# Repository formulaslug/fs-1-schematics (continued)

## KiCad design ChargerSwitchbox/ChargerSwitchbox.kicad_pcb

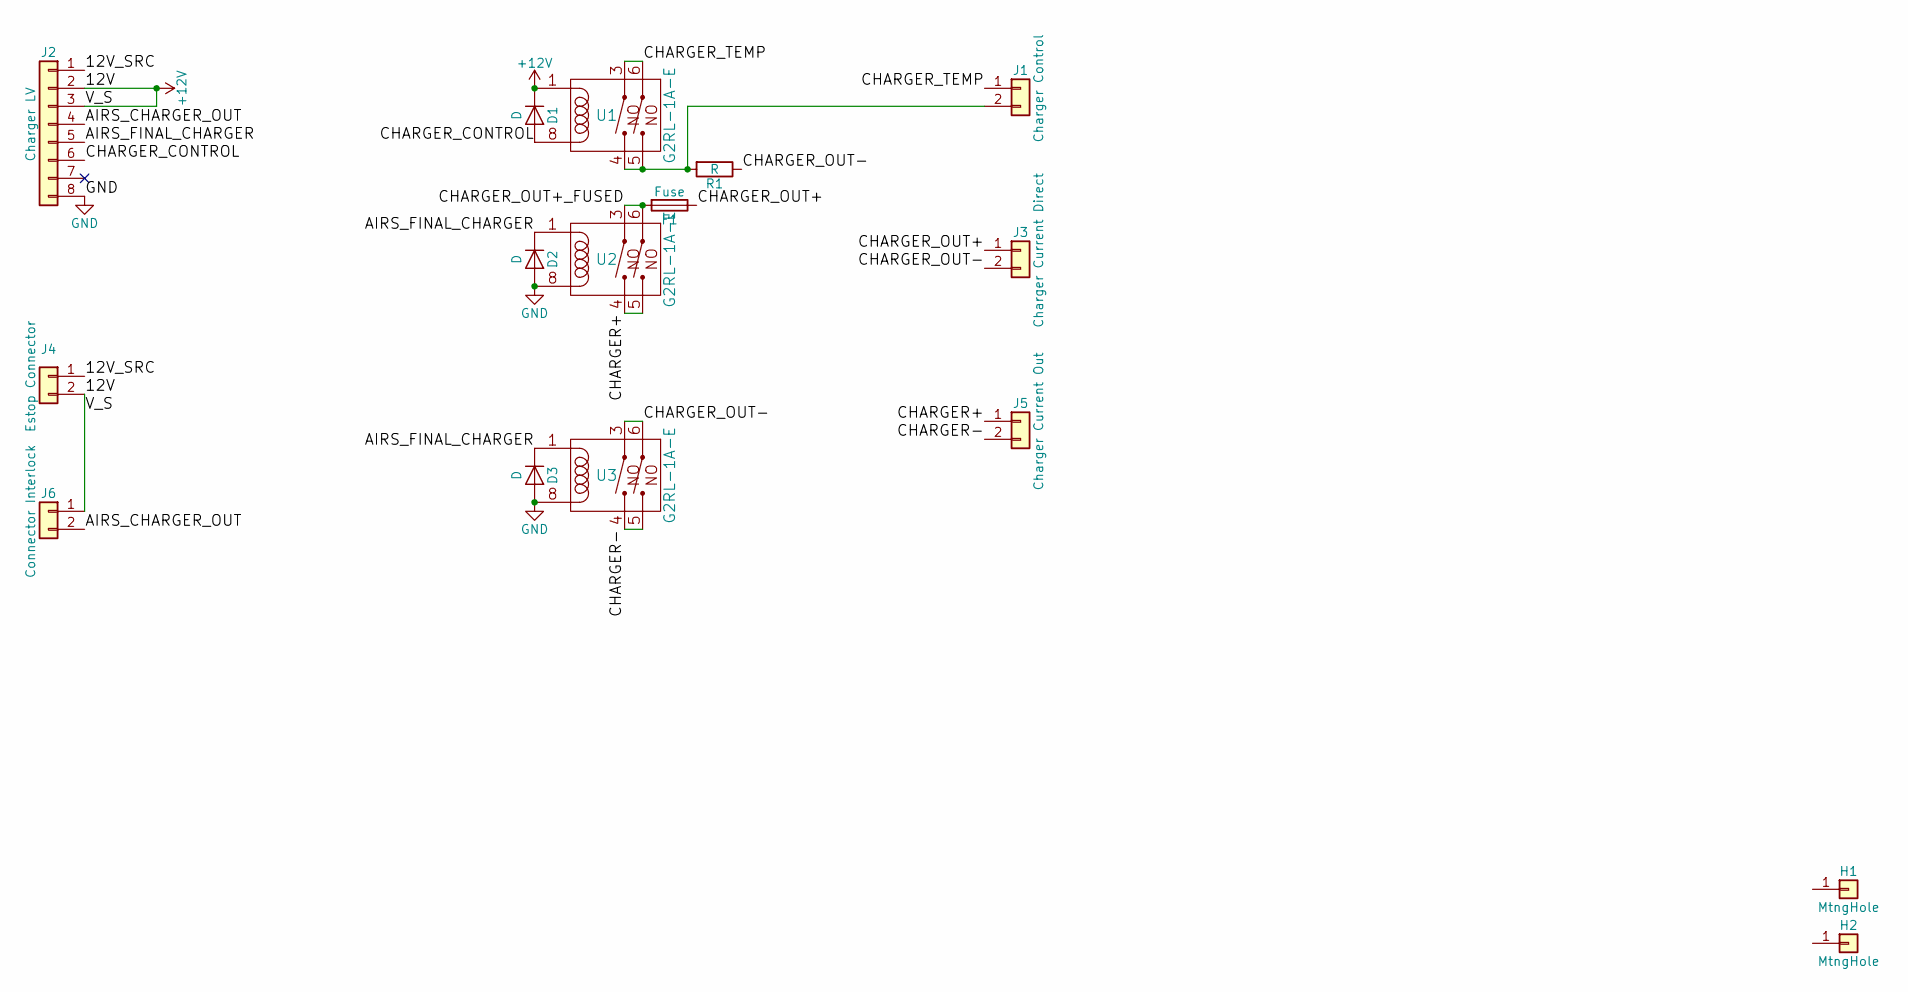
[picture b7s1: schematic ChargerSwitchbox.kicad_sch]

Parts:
D1, D2, D3: D; D_1206
F1: Fuse; Fuseholder5x20_vert
H1, H2: MtngHole; MountingHole_4.5mm
J1: Charger Control; Molex_NanoFit_1x02x2.50mm_Straight
J2: Charger LV; Ampseal - 8 pin
J3: Charger Current Direct; Molex_MiniFit-JR-5556-02A_2x01x4.20mm_Straight
J4: Estop Connector; Molex_NanoFit_1x02x2.50mm_Straight
J5: Charger Current Out; Molex_MiniFit-JR-5556-02A_2x01x4.20mm_Straight
J6: Connector Interlock; Molex_NanoFit_1x02x2.50mm_Straight
R1: R; SMDNetTie
U1, U2, U3: G2RL-1A-E

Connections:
+12V: D1.1 (K), J2.2, J2.3, J4.2, J6.1, U1.1
/12V_SRC: J2.1, J4.1
/AIRS_CHARGER_OUT: J2.4, J6.2
/AIRS_FINAL_CHARGER: D2.1 (K), D3.1 (K), J2.5, U2.1, U3.1
/CHARGER+: J5.1, U2.4, U2.5
/CHARGER-: J5.2, U3.4, U3.5
/CHARGER_CONTROL: D1.2 (A), J2.6, U1.8
/CHARGER_OUT+: F1.1, J3.1
/CHARGER_OUT+_FUSED: F1.2, U2.3, U2.6
/CHARGER_OUT-: J3.2, R1.1, U3.3, U3.6
/CHARGER_TEMP: J1.1, U1.3, U1.6
GND: D2.2 (A), D3.2 (A), J2.8, U2.8, U3.8
unnamed: J1.2, R1.2, U1.4, U1.5

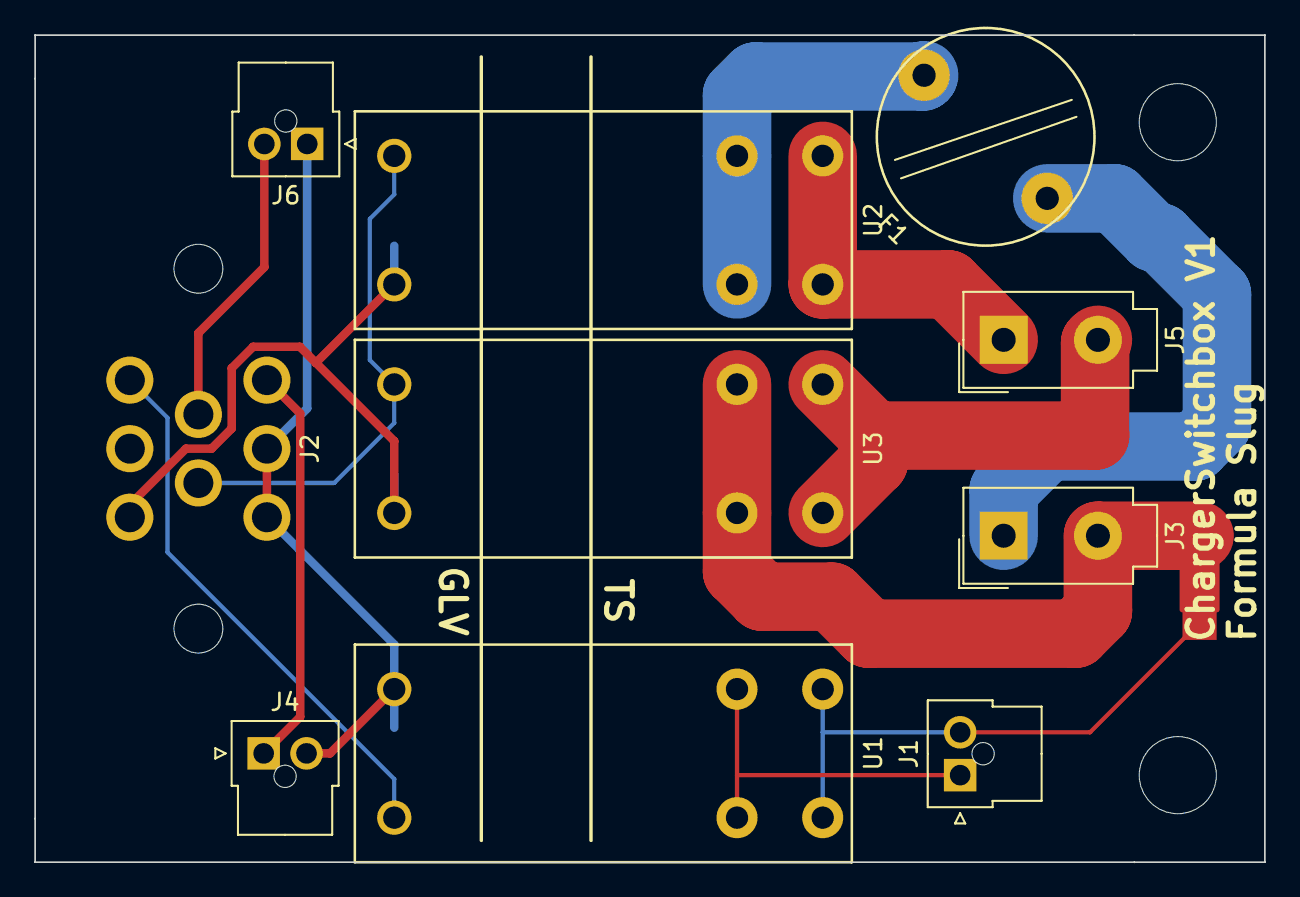
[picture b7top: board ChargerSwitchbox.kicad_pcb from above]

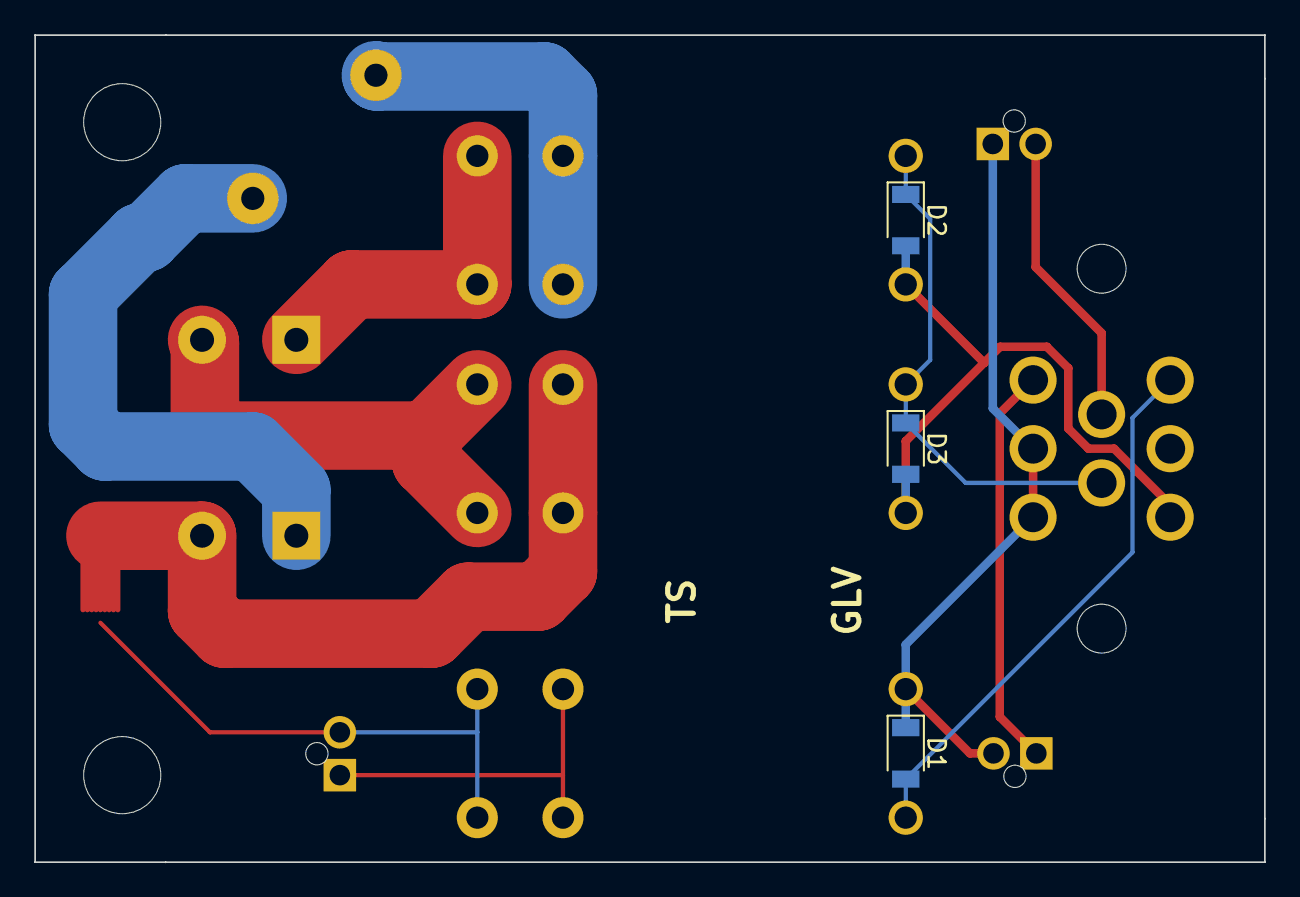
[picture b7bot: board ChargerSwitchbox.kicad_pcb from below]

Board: 2 copper layers, 71.8 x 48.3 mm, 16 parts (3 on the bottom side), 13 nets.

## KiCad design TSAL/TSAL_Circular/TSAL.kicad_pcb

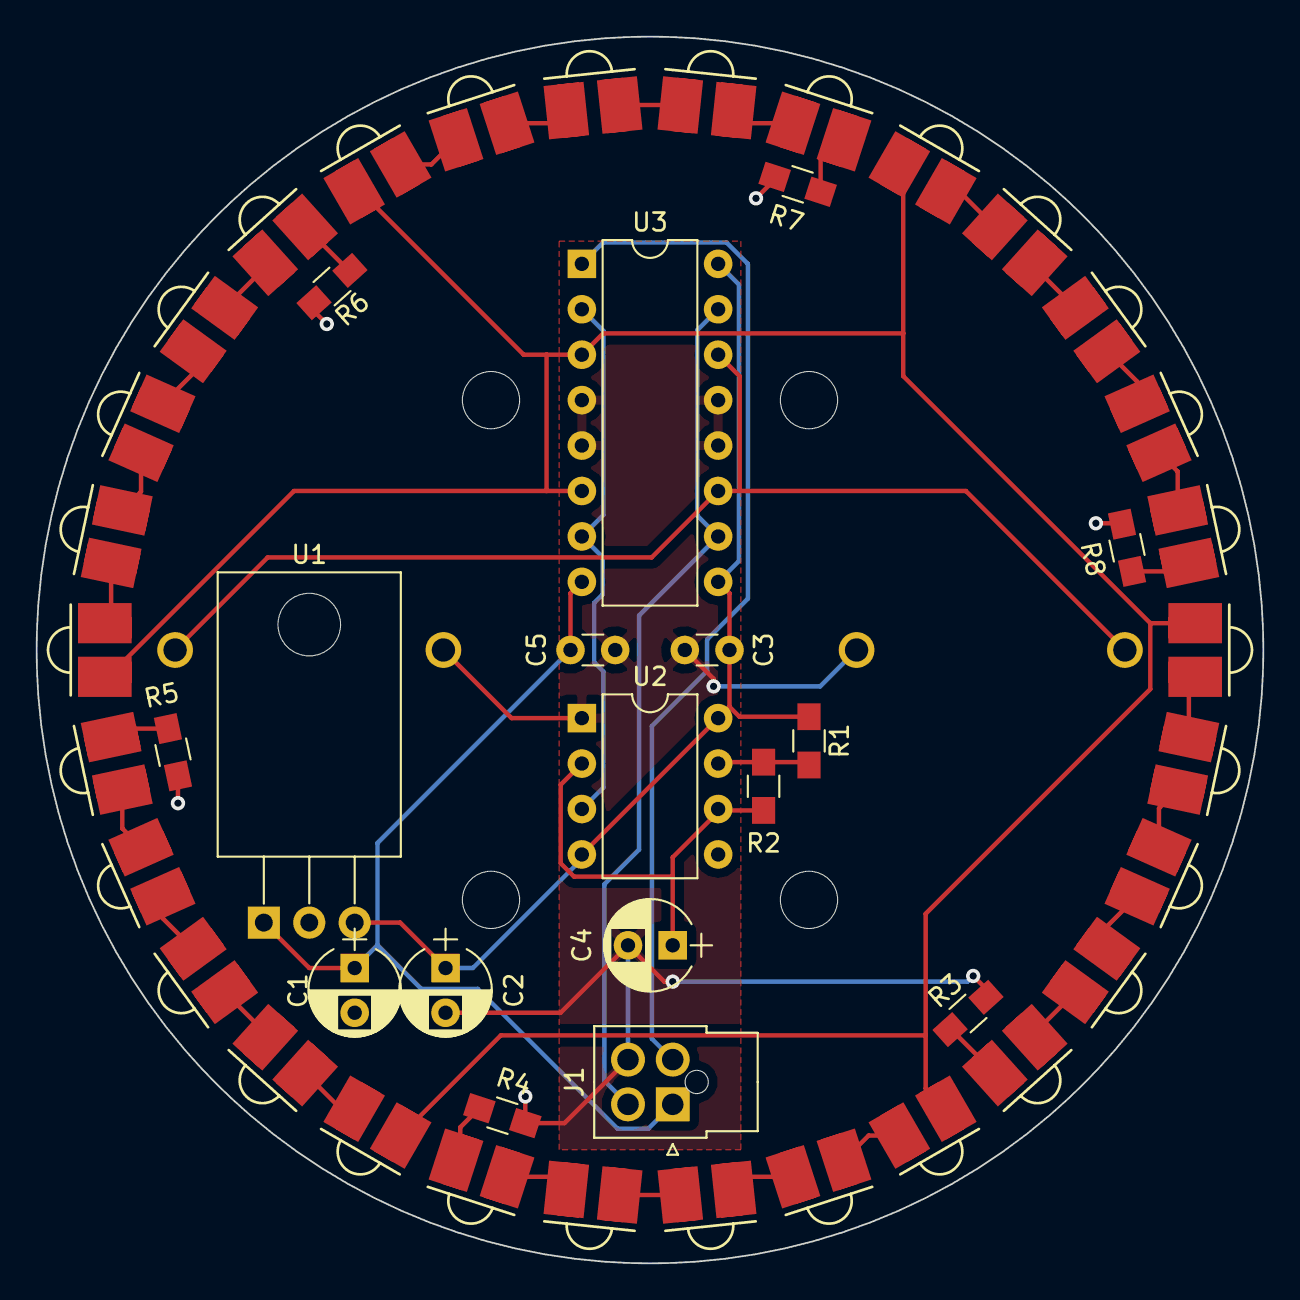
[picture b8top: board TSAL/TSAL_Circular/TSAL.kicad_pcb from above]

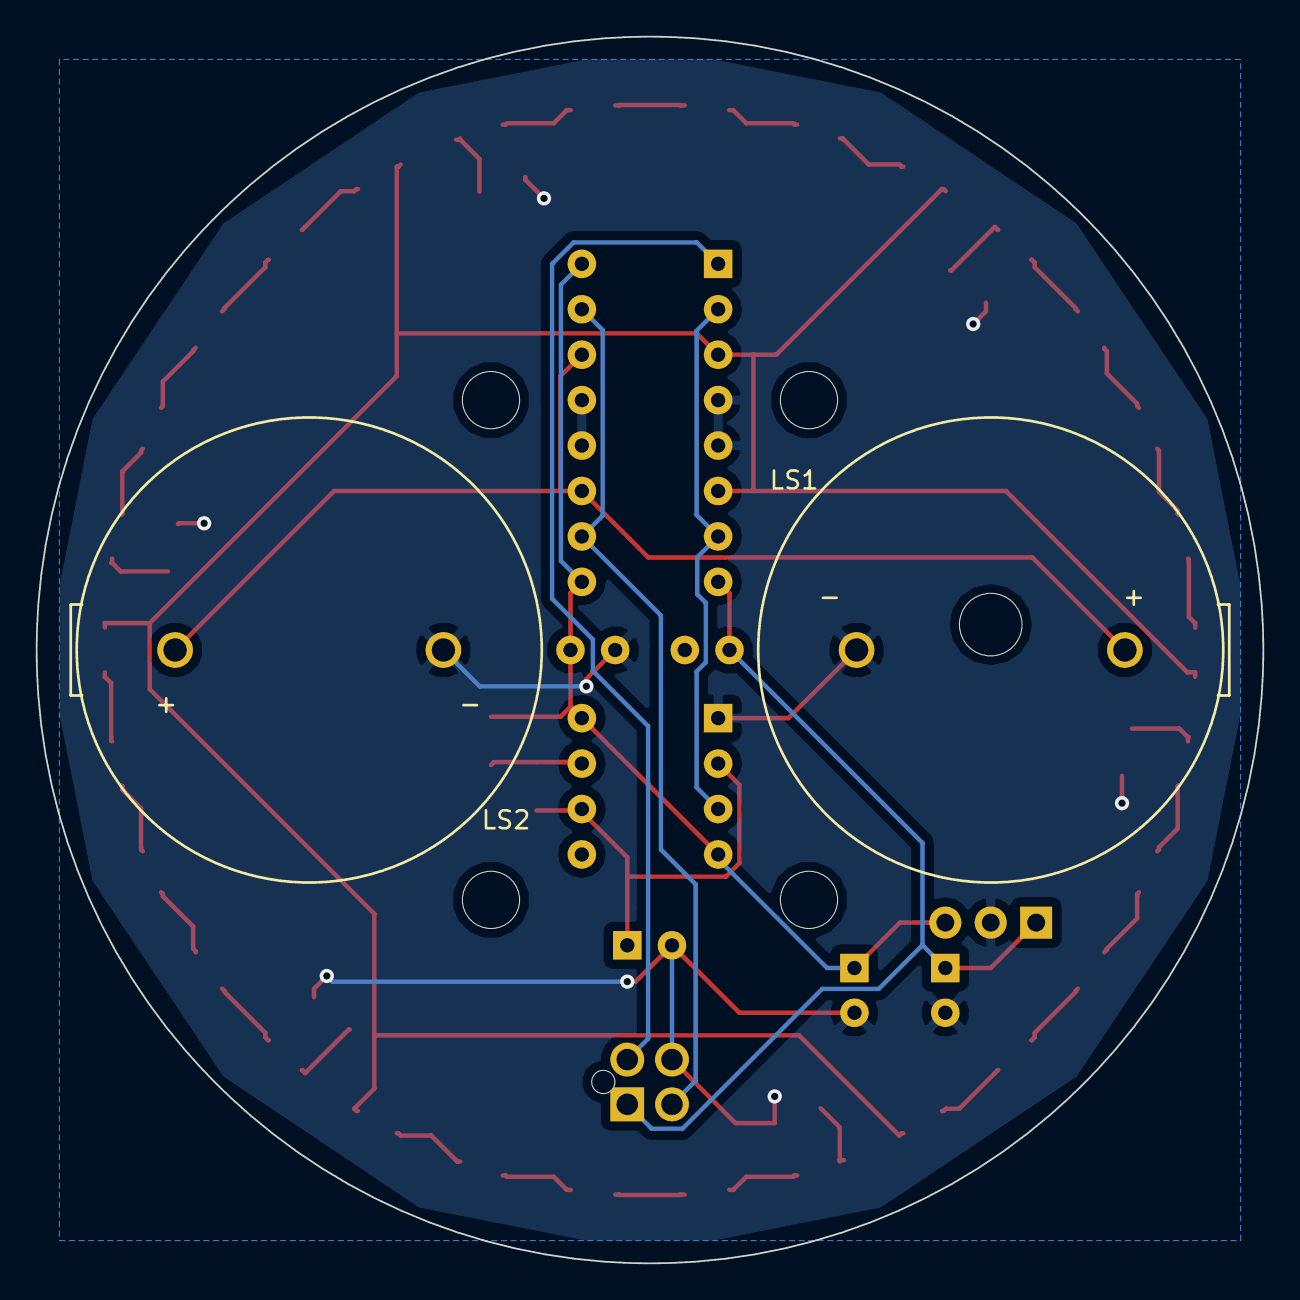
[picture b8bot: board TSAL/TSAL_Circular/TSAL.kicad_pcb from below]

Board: 2 copper layers, 68.6 x 68.6 mm, 53 parts (2 on the bottom side), 40 nets.

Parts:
C1, C4: 10uF; CP_Radial_D5.0mm_P2.50mm
C2: CP; CP_Radial_D5.0mm_P2.50mm
C3, C5: CP; C_Disc_D3.0mm_W1.6mm_P2.50mm
D1, D2, D3, D4, D5, D6, D7, D8, D9, D10, D11, D12, D13, D14, D15, D16, D17, D18, D19, D20, D21, D22, D23, D24, D25, D26, D27, D28, D29, D30: Led_Small; LED_SMD-2
H1, H2, H3, H4: MtngHole; MountingHole_3.2mm_M3
J1: Main Connector; Molex_NanoFit_2x02x2.50mm_Straight
LS1, LS2: Speaker; RTDS_H
R1, R2: 15K; R_0805_HandSoldering
R3, R4, R5, R6, R7, R8: 68; R_0805_HandSoldering
U1: L7805; TO-220-3_Horizontal
U2: LM555; DIP-8_W7.62mm
U3: SN754410; DIP-16_W7.62mm

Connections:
/5V: C2.1, C3.1, R1.1, U1.3, U2.4, U2.8, U3.9, U3.16
/12V: C1.1, C5.1, J1.1, U1.1, U3.8
/GND: C1.2, C2.2, C3.2, C4.2, C5.2, J1.4, LS1.2, LS2.2, R3.2, R4.2, R5.2, R6.2, R7.2, R8.2, U1.2, U2.1, U3.4, U3.5, U3.12, U3.13
/OSC: D1.2, D6.2, D11.2, D16.2, D21.2, D26.2, U3.3, U3.6
/RTDS_H: LS1.1, LS2.1, U3.11, U3.14
/SIG_RTDS: J1.3, U3.10, U3.15
/SIG_TSAL: J1.2, U3.1
unnamed: C4.1, R2.2, U2.2, U2.6
unnamed: D1.1, D2.2
unnamed: D2.1, D3.2
unnamed: D3.1, D4.2
unnamed: D4.1, D5.2
unnamed: D5.1, R3.1
unnamed: D6.1, D7.2
unnamed: D7.1, D8.2
unnamed: D8.1, D9.2
unnamed: D10.1, R4.1
unnamed: D9.1, D10.2
unnamed: D11.1, D12.2
unnamed: D12.1, D13.2
unnamed: D13.1, D14.2
unnamed: D14.1, D15.2
unnamed: D15.1, R5.1
unnamed: D16.1, D17.2
unnamed: D17.1, D18.2
unnamed: D18.1, D19.2
unnamed: D19.1, D20.2
unnamed: D20.1, R6.1
unnamed: D21.1, D22.2
unnamed: D22.1, D23.2
unnamed: D23.1, D24.2
unnamed: D24.1, D25.2
unnamed: D25.1, R7.1
unnamed: D26.1, D27.2
unnamed: D27.1, D28.2
unnamed: D28.1, D29.2
unnamed: D29.1, D30.2
unnamed: D30.1, R8.1
unnamed: R1.2, R2.1, U2.7
unnamed: U2.3, U3.2, U3.7

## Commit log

2017-01-25 Begin working on power electronics box and copied over FS-0 library
2017-01-27 Added brake light to FS library
2017-02-01 Both PEBoard and PEBox, now are separate schematics
2017-02-01 Finish up PEboard
2017-02-02 Add connectors for interlocks for three phase connectors to PEBoard
2017-02-05 Add TSAL schematic from fs-0
2017-02-05 Add Deutsch EEC box pcb package as well as arduino library for STM package
2017-02-05 Start ECU
2017-02-06 Add DIP package MCP2515 to FS library
2017-02-06 Add voltage reg and MCP2515 SPI CAN to FS lib
2017-02-06 Continue working on ECU schematic
2017-02-08 Begin accumulator board, latching for IMD/BMS
2017-02-12 Add 60V switching
2017-02-13 Added Temp Shield
2017-02-15 something idk temp boards or whatever
2017-02-19 Continue BSPD on accumulator board
2017-02-19 Fix library issues
2017-02-21 Add comparators for BSPD
2017-02-21 Begin connectors for Accumulator board
2017-02-22 Add vicor regulator module
2017-02-22 Add actual Vicor file
2017-02-24 Cosmetic work on accumulator board
2017-02-26 Add power symbols and new latching design to Accumulator board
2017-02-28 Add latching circuits for all components
2017-03-01 Add timing delay for fault startup
2017-03-01 Set up 555 timer for new BSPD
2017-03-02 Make BSPD fault-state low and implement startup latching delay
2017-03-02 Add AccumulatorElectronics schematic
2017-03-02 Add BSPD test jumper
2017-03-03 Edit packages for items
2017-03-03 Make BSPD fully fault low
2017-03-04 Add temp board shell and made BSPD fully fault low
2017-03-04 Add more energy meter connectors to PE board, EM may move to accumulator
2017-03-05 Organize ECU sheet better
2017-03-05 Downsize ECU to A4
2017-03-05 Add LV fuse after Vicor
2017-03-06 Add dash
2017-03-06 Add dash button pins to ECU
2017-03-06 Update PE board - move e-meter out and update interlocks
2017-03-12 Added initial schematic for battery temp monitor system
2017-03-12 Move TSAL to PE box
2017-03-13 Add fusing to TSAL line
2017-03-14 Changed MCP3008 to the FS_FINAL version
2017-03-14 Fixed battery temp monitor wiring
2017-03-14 Fix libraries in temp monitor project
2017-03-22 Add dash to library
2017-03-22 Added voltage regulator, diode, and I/O connectors to CTMS
2017-03-29 Revisions for ESF
2017-06-04 Schematic changes from real life testing
2017-06-04 Modify system for changes discovered about relays
2017-06-25 Update based on finalized wire harness
2017-06-25 Added TE Ampseal footprints
2017-06-25 Add board for Dash Switchbox
2017-06-30 Added footprint for latching relay
2017-07-03 Adding bypass caps and adding LV relays to HV board
2017-08-03 Temp Board
2017-08-04 Brake Light
2017-08-27 Begin work on moving ECU to PE box
2017-08-27 Set unix line endings on files
2017-08-27 Enforce line endings with gitattributes file
2017-08-27 Improved 60v threshold circuit for accumulator
2017-08-28 Clean up LV accumulator schematic
    Need to solidify connections between accumulator LV board and temp board
2017-08-30 Add connections to temp board for isolation and fault feedback
2017-09-01 Brake Light Schematic and PCB
2017-09-08 Progress on PE LV and HV boards
    Upgraded to Kicad 4.0.7
2017-09-09 Complete dash switchbox schematic
2017-09-09 Hopefully finalize PCB schematics
2017-09-15 Added hierarchy and templates for markdown docs
2017-09-17 Updated components in temp schematic; re-aligned wiring
2017-09-17 Updated non-modular temp and added SPI isolator chip
2017-09-19 Changed vcc1 (digital supply) of CAN transceiver to 3.3V
2017-09-19 Added bypass cap for HV side of SPI isolator
2017-09-19 Added bypass caps for all SPI ADC chip vref and digital supplies
2017-09-19 Add top-level documentation
2017-09-29 Removed brackets from top level system descriptions
2017-09-30 Cleaned up tracks
2017-10-01 centered LEDs
2017-10-13 Add 3.3v rail to PE HV
2017-10-21 Add wiring for motor sensors
2017-10-21 Fix the connectors between HV and LV boards
2017-12-24 Swapped out vreg for temp system, TS/GLV naming convention, added BMS pull up resistor
2017-12-24 Update to use new latching relays, remove BMS pull up resistor because the relay is the pull up resistor
2018-01-10 Reconfigure dash schematic to take advantage of spare pin
2018-01-13 Add second piezo to TSAL
2018-01-14 Final revision of brake light. Done in Eagle. Info in README
2018-01-15 Completed TSAL schematic and PCB, done in Eagle. NOTE: Ready-to-drive sound NOT implemented yet.
2018-01-16 Added charger control pins and organized optos
2018-01-23 Set footprints for Accumulator HV board, creating necessary ones
2018-01-23 Set footprints for Accumulator LV board, creating necessary ones
2018-02-05 Begin PE/dash footprints, continue with accumulator footprints
2018-02-07 Begin layout of AccumulatorHV board
2018-02-09 AccumulatorLV pcb initial layout
2018-02-10 Dash Switchbox PCB layout
2018-02-12 Work for preparation for autorouting
2018-02-12 Autoroute AccumulatorHV PCB
2018-02-12 Work on LV pcb, having trouble finishing routing
2018-02-12 Revise Accumulator HV and LV, route Dash Switchbox, begin PE HV
2018-02-14 Progress on PE HV PCB layout
2018-02-15 Tweak AccumulatorHV PCB
2018-02-15 Layout and route PE HV board
2018-02-18 Reverse direction of PE HV pcb
2018-02-18 Update footprint cosmetics
2018-02-23 Moved ECU status LEDs to be on the same port
2018-02-23 Completed dual CAN ECU
2018-02-23 WIP: Added all parts for dual CAN ECU and wired some components
2018-02-23 Moved GLV CAN TX/RX to pins available on discovery board
2018-02-25 Lay out rev1 PE LV PCB
2018-02-26 Route rev1 PE LV PCB
2018-02-27 Tweak PE HV board
2018-02-27 Reverse direction of PE LV board
2018-02-27 Update silkscreen component label positioning
2018-02-28 Fixed steering (A-IN), IMD (D-IN), and BSPD (D-OUT) pins
2018-02-28 PE LV Board will be ready to go once routed
    Had to make a couple changes to net size to pass Bay Area Circuit's DFM
2018-02-28 Route V1.0 ECU PCB, should be ready to send for manufacturing
2018-03-01 Add mounting holes to Accumulator HV PCB
2018-03-01 Re-layout Accumulator LV PCB, adding mounting holes
2018-03-01 V2 of PE LV PCB
2018-03-02 Route PE LV PCB with ground plane and vcc plane
2018-03-02 Route PE LV with 4 layers, using center layers as power planes
2018-03-03 Fix grid on the board layout
2018-03-03 Add ground planes to PE HV PCB and add an additional mounting hole
2018-03-03 Fix via size for manufacturing
2018-03-03 Updated TSAL with RTDS. Only needs mounting holes.
2018-03-04 Organized folder paths. Re-did brake light in KiCad. KiCad knowledge overrided eagle knowledge..
2018-03-04 Add more ground/vcc plane bridges to PE LV pcb
2018-03-04 Fix drill sizes for manufacturing on PE HV board
2018-03-04 Add larger fuse to AccumulatorHV board
2018-03-04 Clean out some files from repo
2018-03-05 Add planes to Accumulator LV board
2018-03-05 Create joined PCBs for manufacturing on the same board
    Accumulator one is having problems with the exported files on DFM for some reason
2018-03-06 Finalize the 4 layer PCB
2018-03-06 Select 4 layer version of PE LV board
2018-03-07 Add Charger switchbox
2018-03-07 Tweak routing on boards, add mounting holes to dash switchbox
2018-03-09 Tweak silkscreen labels on boards for final run
2018-03-09 Need to correct Bay Area DFM warnings on TSAL. Brake Light passed and ready to be sent.
2018-03-10 Revise boards based on design review
2018-03-10 Change TSMP resistors
2018-03-11 Tweaks to output schematics for ESF
2018-03-11 Updated TSAL. passed DFM
2018-03-12 Un-fuse TSMPs
2018-03-12 resdesigned tsal. It is circular, much like fs0 tsal.
2018-03-14 Add connections to connectors on PE and Acc LV boards
2018-03-16 redo AccumulatorBoardLV for new accumulator packaging scheme
2018-03-16 Clean up old files from repository
2018-03-19 Reverse connector directions on PE LV board
2018-03-21 update some footprint throughole sizes
2018-03-22 update Arduino (used for STMF3) footprint as well
2018-03-23 edit PCBs based on actual parts that have arrived
2018-03-27 add fuse to CAN+ line on PE HV board
2018-03-27 prepare to re-send PE LV board
2018-03-27 Move LEDs on PE LV board
2018-03-27 fix AccumulatorLV board based on real life testing
2018-03-28 shrink AccumulatorHV PCB
2018-03-29 update for sending out second round of PE LV pcb
2018-03-29 Tweak 60v circuits based on testing results
2018-03-29 push schematic updates for 60V on PE HV
2018-03-29 add circular TSAL with surface mount LEDs
2018-04-03 Add TVS diode and choke to PE HV board
2018-04-08 Update DE relay footprint
2018-04-08 tweak boards slightly
2018-04-11 fix 3.3V reg on ECU footprint
2018-04-21 add diodes to relay coils among other things
2018-04-23 add mounting holes and surface mount resistors to TSAL
2018-04-24 Update 60V circuit some more, on both boards
2018-04-26 move connectors to assist in battery packaging
2018-04-27 temp shield FUCKINGSENDIT
2018-04-28 hopefully finalize PCBs for send to manufacturing
2018-04-29 Edit some component labels and other items for PCB send out
2018-04-29 Add remaining capacitor values to schematics
2018-04-29 add TS/GLV labels to Charger Switchbox pcb
2018-05-01 Fixed temp shields
    Added serial connection between shields bc im dumb and forgot
2018-05-04 update BSPD resistor values
2018-06-04 Final PCB revisions
2019-01-21 Started LTC6811 BMS
2019-01-26 New TSAL beginnings
2019-01-29 TSAL Schematic done
2019-02-11 Updated BMS Schematics
2019-02-13 BMS update
2019-02-13 library stupidity
2019-02-26 Updated BMS
2019-02-27 Begin work on BMS schematic
2019-02-27 Finish layout of TSAL 2019 (ugly edition)
2019-02-27 BMS again
2019-03-05 BMS board v0.1
2019-03-07 Fix TSAL layout to be less garbage
2019-03-10 Add initial BMS master project
2019-03-12 yikes
2019-03-12 Add MSOP-16 Breakout Board
2019-03-31 Update BMS bias resistors and enable pin
2019-04-03 Began BMS slave board
2019-04-03 fixed shit
2019-04-04 BMS update pre-autorouter
2019-04-04 BMS pcb routed
2019-04-07 updated the things
2019-04-08 final lv board routed
2019-04-08 Add termination resistor to isoSPI on Accumulator LV
2019-04-16 Unfucked PELV symbols
2019-04-16 Unfucked Dash
2019-05-29 Torque Vectoring PCB v0.2
2019-05-29 New Molex NanoFit 1x4 footprint that passes DRC ._.
2019-05-30 remapped symbols for PEHV
2020-03-08 CAN Isolator folder
2020-03-08 Moar of previous
2022-12-23 Some changes to hopefully make some projects openable in Kicad 5 and 6
2023-11-04 Make AccLV work in Kicad 4 again
2023-11-04 Convert AccLV to Kicad 7
2023-11-04 Fix AccHV
2023-11-05 Fix up most of the remaining projects
2023-11-05 Fix charger switchbox
